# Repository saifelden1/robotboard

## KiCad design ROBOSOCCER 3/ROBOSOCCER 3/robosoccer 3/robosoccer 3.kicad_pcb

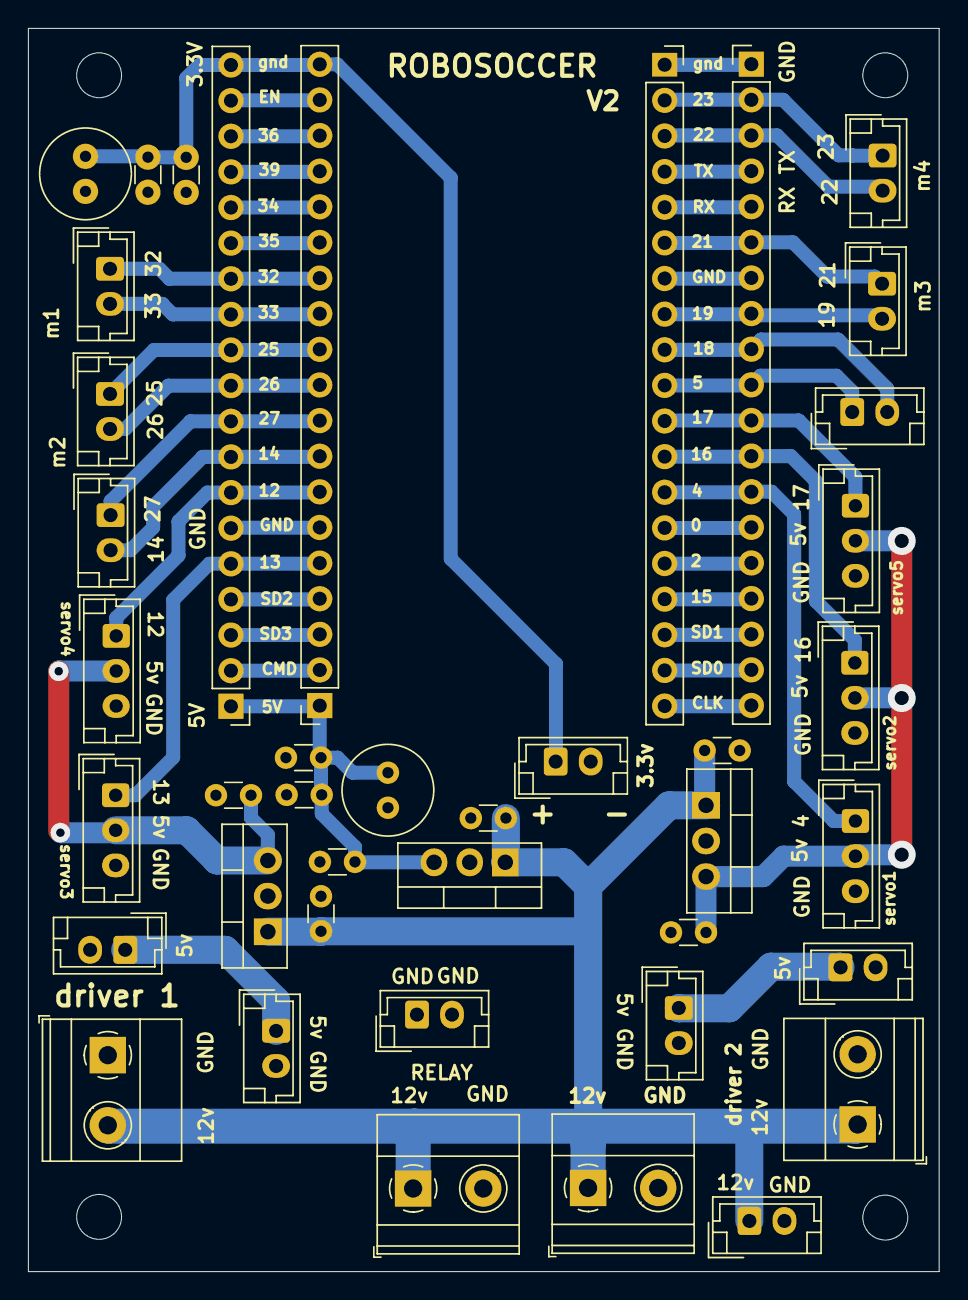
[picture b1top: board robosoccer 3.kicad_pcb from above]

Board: 2 copper layers, 64.9 x 88.6 mm, 45 parts (0 on the bottom side), 41 nets.

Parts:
C1, C2, C4, C5, C6, C7, C8, C9, C12, C13: 0.1uf; C_Disc_D3.0mm_W1.6mm_P2.50mm
C10, C11: 100uf; C_Radial_D6.3mm_H5.0mm_P2.50mm
H1, H2, H3, H4: MountingHole; MountingHole_3.2mm_M3
J1, J2: Conn_01x19_Pin; PinSocket_1x19_P2.54mm_Vertical
J3, J22, J23: battery conn; TerminalBlock_Phoenix_MKDS-1,5-2_1x02_P5.00mm_Horizontal
J4, J5, J6, J7, J8, J9, J21, J24, J25, J26: 5V D1; JST_EH_B2B-EH-A_1x02_P2.50mm_Vertical
J10, J19: servo 1; JST_EH_B3B-EH-A_1x03_P2.50mm_Vertical
J11, J20: servo2; JST_EH_B3B-EH-A_1x03_P2.50mm_Vertical
J12: servo3; JST_EH_B3B-EH-A_1x03_P2.50mm_Vertical
J13, J14: Conn_01x19_Pin; PinHeader_1x19_P2.54mm_Vertical
J15: 5V D2; JST_EH_B2B-EH-A_1x02_P2.50mm_Vertical
J16: battery conn; JST_EH_B2B-EH-A_1x02_P2.50mm_Vertical
J17: 12V; JST_EH_B2B-EH-A_1x02_P2.50mm_Vertical
J18: RELAT CON; TerminalBlock_Phoenix_MKDS-1,5-2_1x02_P5.00mm_Horizontal
U1, U2, U3: L7805; TO-220-3_Vertical

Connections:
0: J1.14, J13.14
2: J1.15, J13.15
3.3V: C4.1, C9.1, C10.1, J2.19, J14.19, J16.1
4: J1.13, J11.1, J13.13
5: J1.10, J9.1, J13.10
5v-1 2 5: C6.1, J10.2, J11.2, J20.2, U1.3 (OUT)
5v-3 4: C2.1, J12.2, J19.2, U3.3 (OUT)
5v-ESP: C8.1, C11.1, C12.1, C13.1, J2.1, J14.1, U2.3 (OUT)
5v-d1: J7.1, J15.1
5v-d2: J4.1, J21.1
12: J2.7, J14.7, J19.1
12v: C1.1, C5.1, C7.1, J3.1, J17.1, J18.1, J22.1, J23.2, U1.1 (IN), U2.1 (IN), U3.1 (IN)
13: J2.5, J12.1, J14.5
14: J2.8, J6.2, J14.8
15: J1.16, J13.16
16: J1.12, J10.1, J13.12
17: J1.11, J13.11, J20.1
18: J1.9, J9.2, J13.9
19: J1.8, J13.8, J25.2
21: J1.6, J13.6, J25.1
22: J1.3, J8.2, J13.3
23: J1.2, J8.1, J13.2
25: J2.11, J14.11, J24.1
26: J2.10, J14.10, J24.2
27: J2.9, J6.1, J14.9
32: J2.13, J5.1, J14.13
33: J2.12, J5.2, J14.12
34: J2.15, J14.15
35: J2.14, J14.14
36: J2.17, J14.17
39: J2.16, J14.16
CLK: J1.19, J13.19
CMD: J2.2, J14.2
EN: J2.18, J14.18
GND: C1.2, C2.2, C4.2, C5.2, C6.2, C7.2, C8.2, C9.2, C10.2, C11.2, C12.2, C13.2, J1.1, J1.7, J2.6, J3.2, J4.2, J7.2, J10.3, J11.3, J12.3, J13.1, J13.7, J14.6, J15.2, J16.2, J17.2, J18.2, J19.3, J20.3, J21.2, J22.2, J23.1, J26.1, J26.2, U1.2 (GND), U2.2 (GND), U3.2 (GND)
RX: J1.5, J13.5
SD0: J1.18, J13.18
SD1: J1.17, J13.17
SD2: J2.4, J14.4
SD3: J2.3, J14.3
TX: J1.4, J13.4

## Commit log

2025-04-10 Create human
